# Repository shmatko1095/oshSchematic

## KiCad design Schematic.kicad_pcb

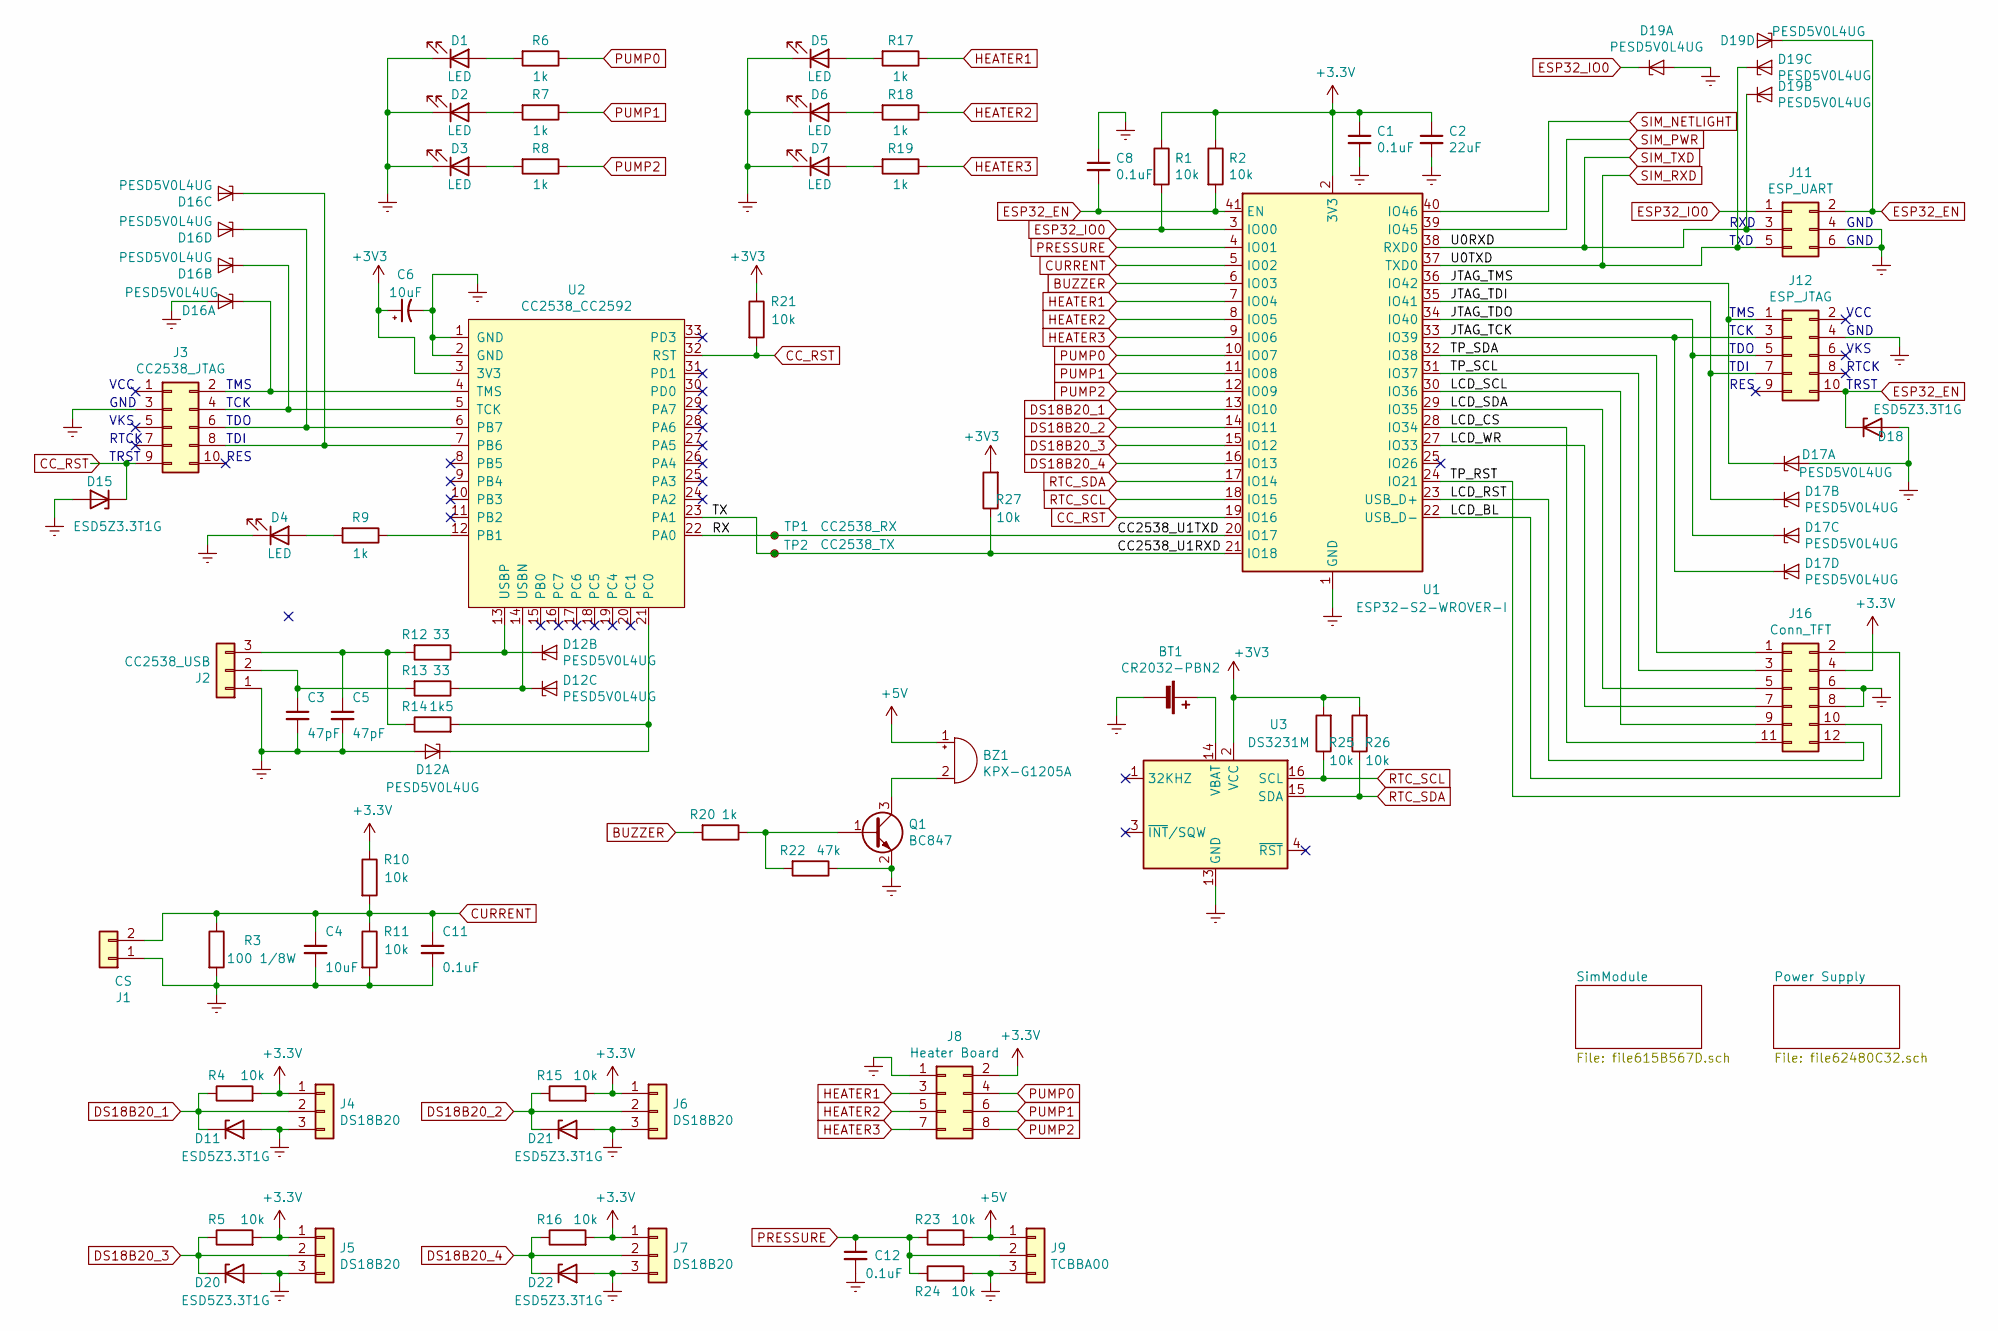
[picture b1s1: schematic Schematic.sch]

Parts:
BT1: CR2032-PBN2; Battery_Panasonic_CR2032-VS1N_Vertical_CircularHoles
BZ1: KPX-G1205A; Buzzer_12x9.5RM7.6
C1, C8, C11, C12: 0.1uF; C_0805_2012Metric
C2: 22uF; C_1206_3216Metric
C3, C5: 47pF; C_0805_2012Metric
C4, C6: 10uF; C_0805_2012Metric
D1, D2, D3, D4, D5, D6, D7: LED; LED_0805_2012Metric
D11, D15, D18, D20, D21, D22: ESD5Z3.3T1G; D_SOD-523
D12, D16, D17, D19: PESD5V0L4UG; SOT-353_SC-70-5
J1: CS; PinSocket_1x02_P2.54mm_Vertical
J2: CC2538_USB; PinSocket_1x03_P2.54mm_Vertical
J3: CC2538_JTAG; PinHeader_2x05_P2.54mm_Vertical
J4, J5, J6, J7: DS18B20; PinSocket_1x03_P2.54mm_Vertical
J8: Heater Board; PinSocket_2x04_P2.54mm_Vertical
J9: TCBBA00; PinSocket_1x03_P2.54mm_Vertical
J11: ESP_UART; PinHeader_2x03_P2.54mm_Vertical
J12: ESP_JTAG; PinHeader_2x05_P2.54mm_Vertical
J16: Conn_TFT; PinHeader_2x06_P1.27mm_Vertical
Q1: BC847; SOT-23
R1, R2, R4, R5, R10, R11, R15, R16, R21, R23, R24, R25, R26, R27: 10k; R_0805_2012Metric
R3: 100 1/8W; R_1206_3216Metric
R6, R7, R8, R9, R17, R18, R19, R20: 1k; R_0805_2012Metric
R12, R13: 33; R_0805_2012Metric
R14: 1k5; R_0805_2012Metric
R22: 47k; R_0805_2012Metric
TP1: CC2538_RX; TestPoint_Pad_D1.5mm
TP2: CC2538_TX; TestPoint_Pad_D1.5mm
U1: ESP32-S2-WROVER-I; ESP32-S2-WROVER
U2: CC2538_CC2592
U3: DS3231M; SOIC-16W_7.5x10.3mm_P1.27mm

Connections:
+5V: BZ1.1 (-), J9.1, R23.2; also elsewhere on the board
/CC2538_U1RXD: R27.1, TP2.1, U1.21 (IO18), U2.23 (PA1)
/CC2538_U1TXD: TP1.1, U1.20 (IO17), U2.22 (PA0)
/JTAG_TCK: D17.5 (K4), J12.3, U1.33 (IO39)
/JTAG_TDI: D17.3 (K2), J12.7, U1.35 (IO41)
/JTAG_TDO: D17.4 (K3), J12.5, U1.34 (IO40)
/JTAG_TMS: D17.1 (K1), J12.1, U1.36 (IO42)
/LCD_BL: J16.10, U1.22 (USB_D-)
/LCD_CS: J16.11, U1.28 (IO34)
/LCD_RST: J16.12, U1.23 (USB_D+)
/LCD_SCL: J16.9, U1.30 (IO36)
/LCD_SDA: J16.5, U1.29 (IO35)
/LCD_WR: J16.7, U1.27 (IO33)
/TP_RST: J16.2, U1.24 (IO21)
/TP_SCL: J16.3, U1.31 (IO37)
/TP_SDA: J16.1, U1.32 (IO38)
BUZZER: R20.2, U1.6 (IO03)
CC_RST: D15.1 (K), J3.9, R21.2, U1.19 (IO16), U2.32 (RST)
CURRENT: C4.1, C11.1, J1.2, R3.1, R10.2, R11.1, U1.5 (IO02)
DS18B20_1: D11.1 (K), J4.2, R4.1, U1.13 (IO10)
DS18B20_2: D21.1 (K), J6.2, R15.1, U1.14 (IO11)
DS18B20_3: D20.1 (K), J5.2, R5.1, U1.15 (IO12)
DS18B20_4: D22.1 (K), J7.2, R16.1, U1.16 (IO13)
ESP32_EN: C8.2, D18.1 (K), D19.5 (K4), J11.2, J12.10, R2.2, U1.41 (EN)
ESP32_IO0: D19.1 (K1), J11.1, R1.2, U1.3 (IO00)
Earth: BT1.2 (-), C1.2, C2.2, C3.2, C4.2, C5.2, C6.2, C8.1, C11.2, C12.2, D1.1 (K), D2.1 (K), D3.1 (K), D4.1 (K), D5.1 (K), D6.1 (K), D7.1 (K), D11.2 (A), D12.2 (A), D15.2 (A), D16.2 (A), D17.2 (A), D18.2 (A), D19.2 (A), D20.2 (A), D21.2 (A), D22.2 (A), J1.1, J2.1, J3.3, J4.3, J5.3, J6.3, J7.3, J8.1, J9.3, J11.4, J11.6, J12.4, J16.6, J16.8, Q1.2 (E), R3.2, R11.2, R22.1, R24.2, U1.1 (GND), U1.26 (GND), U1.42 (GND), U1.43 (GND), U2.1 (GND), U2.2 (GND), U3.5 (GND), U3.6 (GND), U3.7 (GND), U3.8 (GND), U3.9 (GND), U3.10 (GND), U3.11 (GND), U3.12 (GND), U3.13 (GND); also elsewhere on the board
HEATER1: J8.3, R17.1, U1.7 (IO04)
HEATER2: J8.5, R18.1, U1.8 (IO05)
HEATER3: J8.7, R19.1, U1.9 (IO06)
unnamed: BT1.1 (+), U3.14 (VBAT)
unnamed: BZ1.2 (+), Q1.3 (C)
unnamed: C3.1, J2.2, R13.2
unnamed: C5.1, J2.3, R12.2, R14.1
unnamed: D1.2 (A), R6.2
unnamed: D2.2 (A), R7.2
unnamed: D3.2 (A), R8.2
unnamed: D4.2 (A), R9.2
unnamed: D5.2 (A), R17.2
unnamed: D6.2 (A), R18.2
unnamed: D7.2 (A), R19.2
unnamed: D12.1 (K1), R14.2, U2.21 (PC0)
unnamed: D12.3 (K2), R12.1, U2.13 (USBP)
unnamed: D12.4 (K3), R13.1, U2.14 (USBN)
unnamed: D16.1 (K1), J3.2, U2.4 (TMS)
unnamed: D16.3 (K2), J3.4, U2.5 (TCK)
unnamed: D16.4 (K3), J3.8, U2.7 (PB6)
unnamed: D16.5 (K4), J3.6, U2.6 (PB7)
unnamed: Q1.1 (B), R20.1, R22.2
unnamed: R9.1, U2.12 (PB1)
PRESSURE: C12.1, J9.2, R23.1, R24.1, U1.4 (IO01)
PUMP0: J8.4, R6.1, U1.10 (IO07)
PUMP1: J8.6, R7.1, U1.11 (IO08)
PUMP2: J8.8, R8.1, U1.12 (IO09)
RTC_SCL: R25.1, U1.18 (IO15), U3.16 (SCL)
RTC_SDA: R26.1, U1.17 (IO14), U3.15 (SDA)
SIM_NETLIGHT: U1.40 (IO46); also elsewhere on the board
SIM_PWR: U1.39 (IO45); also elsewhere on the board
SIM_RXD: D19.4 (K3), J11.5, U1.37 (TXD0); also elsewhere on the board
SIM_TXD: D19.3 (K2), J11.3, U1.38 (RXD0); also elsewhere on the board

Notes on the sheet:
VCC
TRST
RTCK
GND
VKS
TMS
TCK
TDO
TDI
RES
RXD
TXD

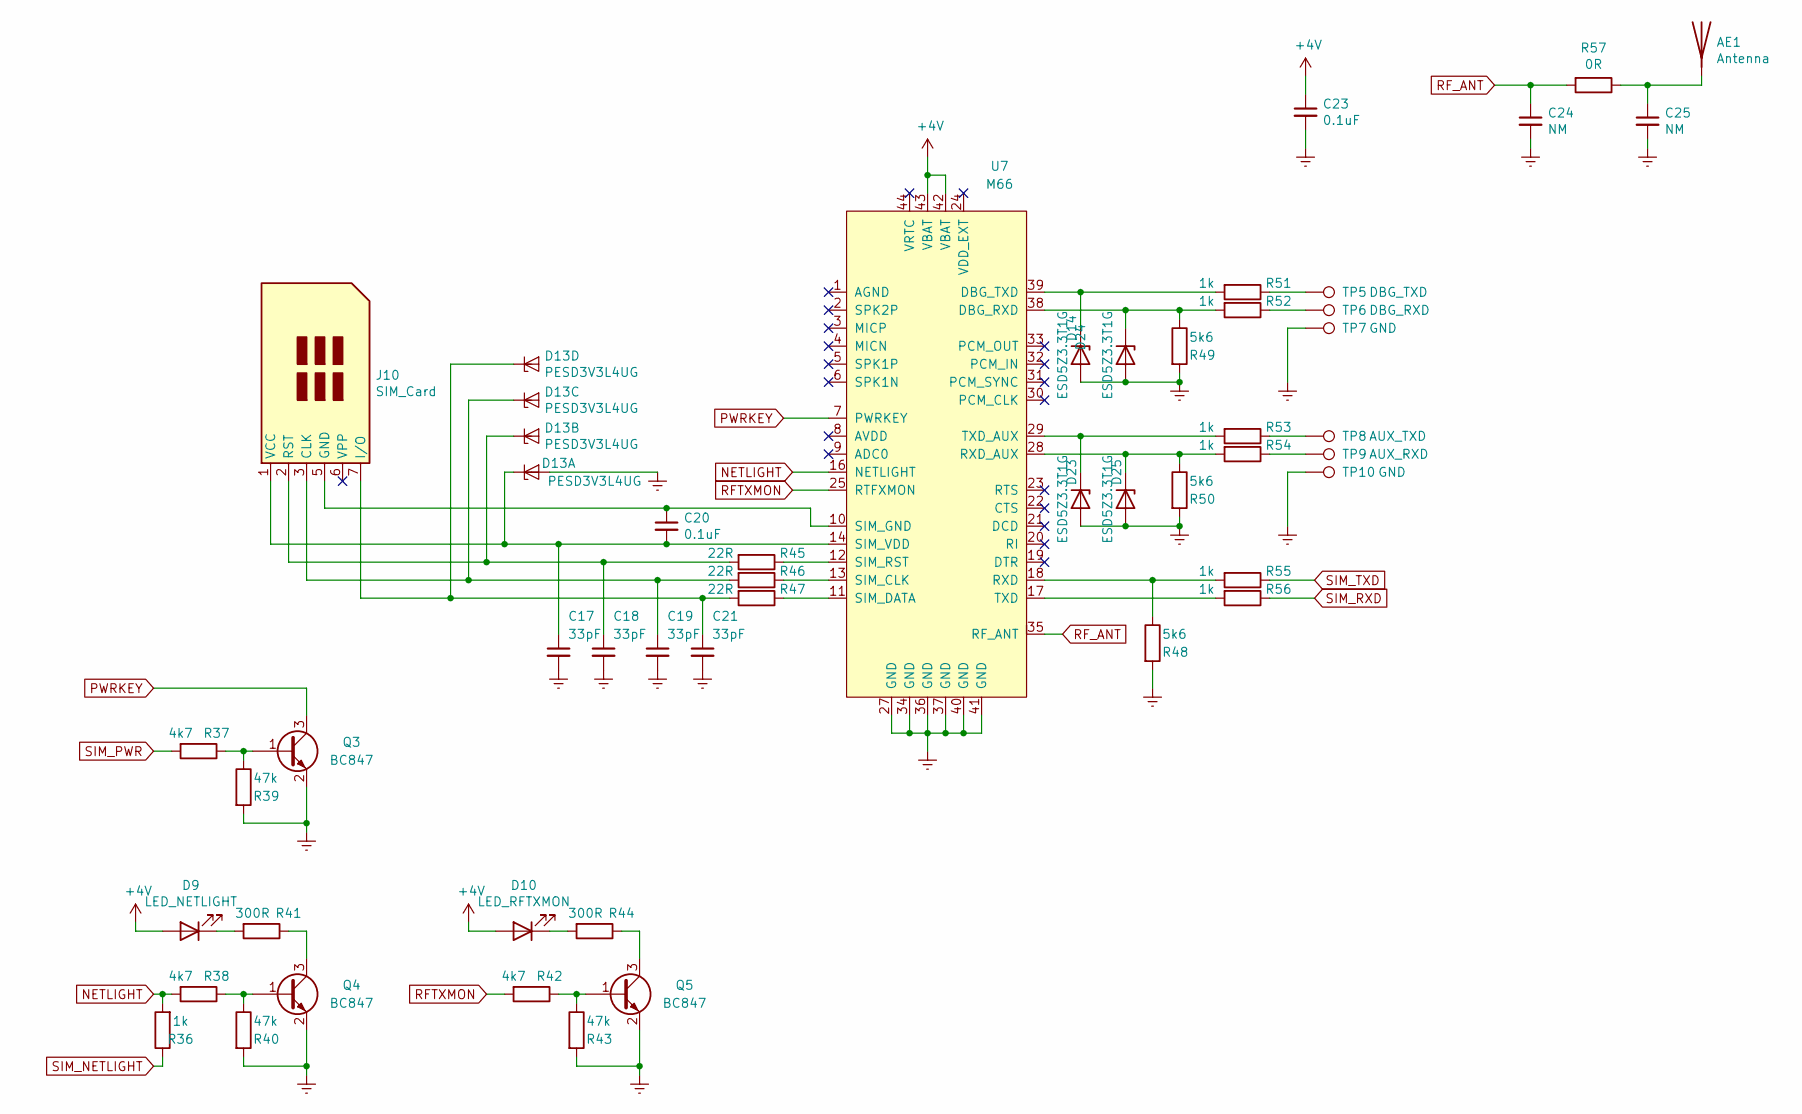
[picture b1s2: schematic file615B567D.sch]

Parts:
AE1: Antenna; SolderWire-0.1sqmm_1x01_D0.4mm_OD1mm_Relief
C17, C18, C19, C21: 33pF; C_0805_2012Metric
C20, C23: 0.1uF; C_0805_2012Metric
C24, C25: NM; C_0805_2012Metric
D9: LED_NETLIGHT; LED_0805_2012Metric
D10: LED_RFTXMON; LED_0805_2012Metric
D13: PESD3V3L4UG; SOT-353_SC-70-5
D14, D23, D24, D25: ESD5Z3.3T1G; D_SOD-523
J10: SIM_Card; NANOSIM_HINGE_1.5H
Q3, Q4, Q5: BC847; SOT-23
R36, R51, R52, R53, R54, R55, R56: 1k; R_0805_2012Metric
R37, R38, R42: 4k7; R_0805_2012Metric
R39, R40, R43: 47k; R_0805_2012Metric
R41, R44: 300R; R_0805_2012Metric
R45, R46, R47: 22R; R_0805_2012Metric
R48, R49, R50: 5k6; R_0805_2012Metric
R57: 0R; R_0805_2012Metric
TP5: DBG_TXD; TestPoint_Pad_1.0x1.0mm
TP6: DBG_RXD; TestPoint_Pad_1.0x1.0mm
TP7, TP10: GND; TestPoint_Pad_1.0x1.0mm
TP8: AUX_TXD; TestPoint_Pad_1.0x1.0mm
TP9: AUX_RXD; TestPoint_Pad_1.0x1.0mm
U7: M66; Quectel_M66

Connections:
+4V: C23.1, D9.2 (A), D10.2 (A), U7.42 (VBAT), U7.43 (VBAT); also elsewhere on the board
Earth: C17.2, C18.2, C19.2, C21.2, C23.2, C24.2, C25.2, D13.2 (A), D14.2 (A), D23.2 (A), D24.2 (A), D25.2 (A), Q3.2 (E), Q4.2 (E), Q5.2 (E), R39.2, R40.2, R43.2, R48.2, R49.2, R50.2, TP7.1, TP10.1, U7.27 (GND), U7.34 (GND), U7.36 (GND), U7.37 (GND), U7.40 (GND), U7.41 (GND); also elsewhere on the board
NETLIGHT: R36.2, R38.2, U7.16 (NETLIGHT)
unnamed: AE1.1, C25.1, R57.1
unnamed: C17.1, C20.2, D13.1 (K1), J10.1 (VCC), U7.14 (SIM_VDD)
unnamed: C18.1, D13.3 (K2), J10.2 (RST), R45.2
unnamed: C19.1, D13.4 (K3), J10.3 (CLK), R46.2
unnamed: C20.1, J10.5 (GND), U7.10 (SIM_GND)
unnamed: C21.1, D13.5 (K4), J10.7 (I/O), R47.2
unnamed: D9.1 (K), R41.2
unnamed: D10.1 (K), R44.2
unnamed: D14.1 (K), R51.2, U7.39 (DBG_TXD)
unnamed: D23.1 (K), R53.2, U7.29 (TXD_AUX)
unnamed: D24.1 (K), R49.1, R52.2, U7.38 (DBG_RXD)
unnamed: D25.1 (K), R50.1, R54.2, U7.28 (RXD_AUX)
unnamed: Q3.1 (B), R37.1, R39.1
unnamed: Q4.1 (B), R38.1, R40.1
unnamed: Q4.3 (C), R41.1
unnamed: Q5.1 (B), R42.1, R43.1
unnamed: Q5.3 (C), R44.1
unnamed: R45.1, U7.12 (SIM_RST)
unnamed: R46.1, U7.13 (SIM_CLK)
unnamed: R47.1, U7.11 (SIM_DATA)
unnamed: R48.1, R55.2, U7.18 (RXD)
unnamed: R51.1, TP5.1
unnamed: R52.1, TP6.1
unnamed: R53.1, TP8.1
unnamed: R54.1, TP9.1
unnamed: R56.2, U7.17 (TXD)
PWRKEY: Q3.3 (C), U7.7 (PWRKEY)
RFTXMON: R42.2, U7.25 (RTFXMON)
RF_ANT: C24.1, R57.2, U7.35 (RF_ANT)
SIM_NETLIGHT: R36.1; also elsewhere on the board
SIM_PWR: R37.2; also elsewhere on the board
SIM_RXD: R56.1; also elsewhere on the board
SIM_TXD: R55.1; also elsewhere on the board

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
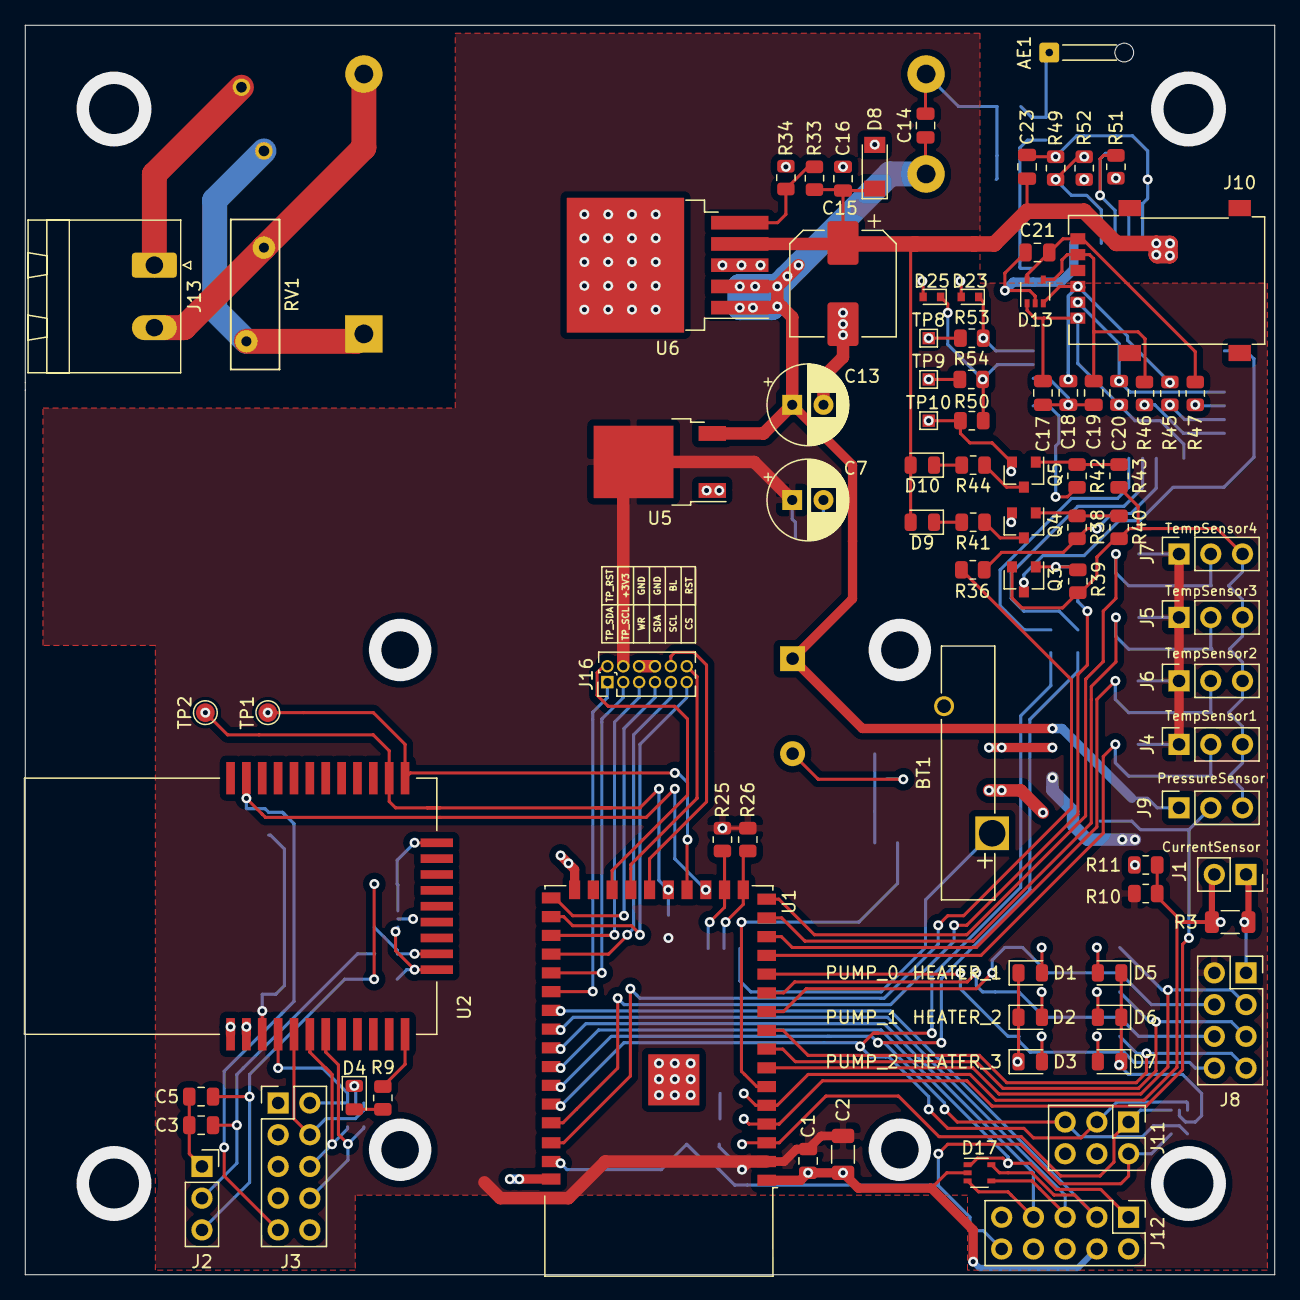
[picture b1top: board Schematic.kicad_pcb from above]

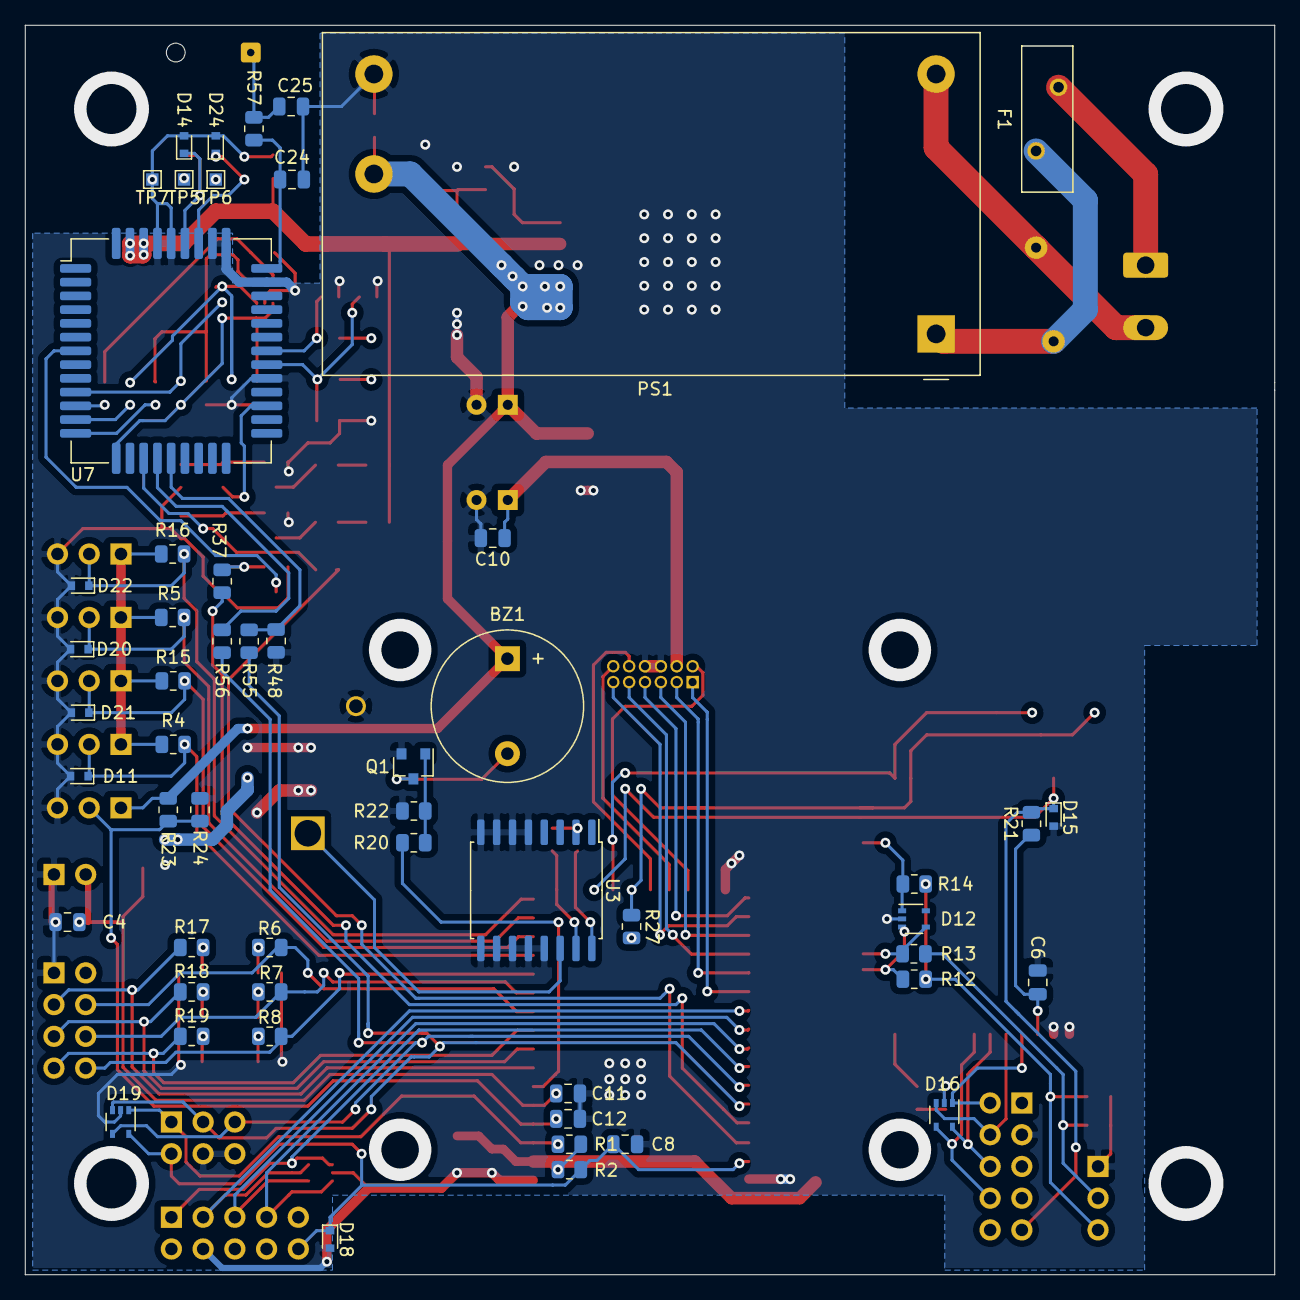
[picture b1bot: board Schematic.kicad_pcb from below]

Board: 2 copper layers, 100.0 x 100.0 mm, 137 parts (54 on the bottom side), 95 nets.

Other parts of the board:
C7, C13: 470uF; CP_Radial_D6.3mm_P2.50mm
C10: 10uF; C_0805_2012Metric
C14, C16: 100nF; C_0805_2012Metric
C15: SMDCAP-470mkf - 10v; CP_Elec_8x10
D8: BZV55B5V1; D_MiniMELF
F1: 3,6x10 0.5A; Fuse_BelFuse_0ZRE0033FF_L11.4mm_W3.8mm
J13: 220V; PhoenixContact_MSTBA_2,5_2-G_1x02_P5.00mm_Horizontal
PS1: IRM-20-5; Converter_ACDC_MeanWell_IRM-20-xx_THT
R33: 124k; R_0805_2012Metric
R34: 56k; R_0805_2012Metric
RV1: 10D561K; RV_Disc_D12mm_W3.9mm_P7.5mm
U5: LD1086DT33TR; TO-252-2
U6: MIC29302WU; TO-263-5_TabPin3

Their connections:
+4V: C15.1, C16.1, D8.1, R33.2, U6.4; also elsewhere on the board
+5V: C13.1, C14.1, PS1.4, U5.3, U6.1, U6.2; also elsewhere on the board
/Power Supply/L: F1.2, J13.1
/Power Supply/N: J13.2, PS1.2, RV1.2
Earth: C7.2, C10.2, C13.2, C14.2, C15.2, C16.2, D8.2, PS1.3, R34.1, U5.1, U6.3; also elsewhere on the board
unnamed: F1.1, PS1.1, RV1.1
unnamed: R33.1, R34.2, U6.5

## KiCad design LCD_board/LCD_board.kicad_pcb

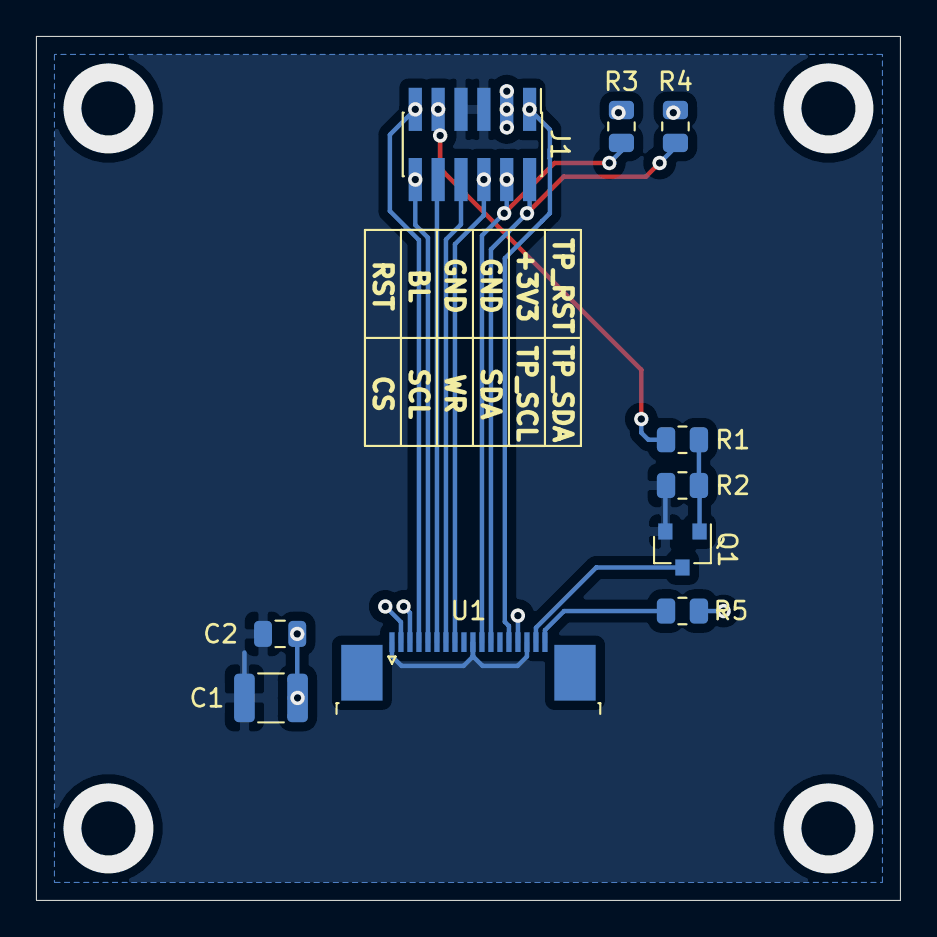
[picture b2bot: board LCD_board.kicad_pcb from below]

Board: 2 copper layers, 48.0 x 48.0 mm, 10 parts (10 on the bottom side), 14 nets.

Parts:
C1: C; C_1210_3225Metric
C2: C; C_0805_2012Metric
J1: Conn_02x06; PinHeader_2x06_P1.27mm_Vertical_SMD
Q1: BC847; SOT-23
R1, R2, R3, R4, R5: R; R_0805_2012Metric
U1: TT130RGC17B; TE_1-1734839-8_1x18-1MP_P0.5mm_Horizontal

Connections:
+3V3: C1.1, C2.1, J1.3, R3.2, R4.2, R5.2, U1.2, U1.3, U1.15
Earth: C1.2, C2.2, J1.5, J1.7, Q1.2, R2.1, U1.1, U1.10, U1.16
unnamed: J1.1, U1.14
unnamed: J1.2, R4.1, U1.12
unnamed: J1.4, R3.1, U1.11
unnamed: J1.6, U1.8
unnamed: J1.8, U1.7
unnamed: J1.9, R1.1
unnamed: J1.10, U1.6
unnamed: J1.11, U1.4
unnamed: J1.12, U1.5
unnamed: Q1.1, R1.2, R2.2
unnamed: Q1.3, U1.17
unnamed: R5.1, U1.18

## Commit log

2021-10-18 OSH schematix rev-0.1 is ready and ordered
